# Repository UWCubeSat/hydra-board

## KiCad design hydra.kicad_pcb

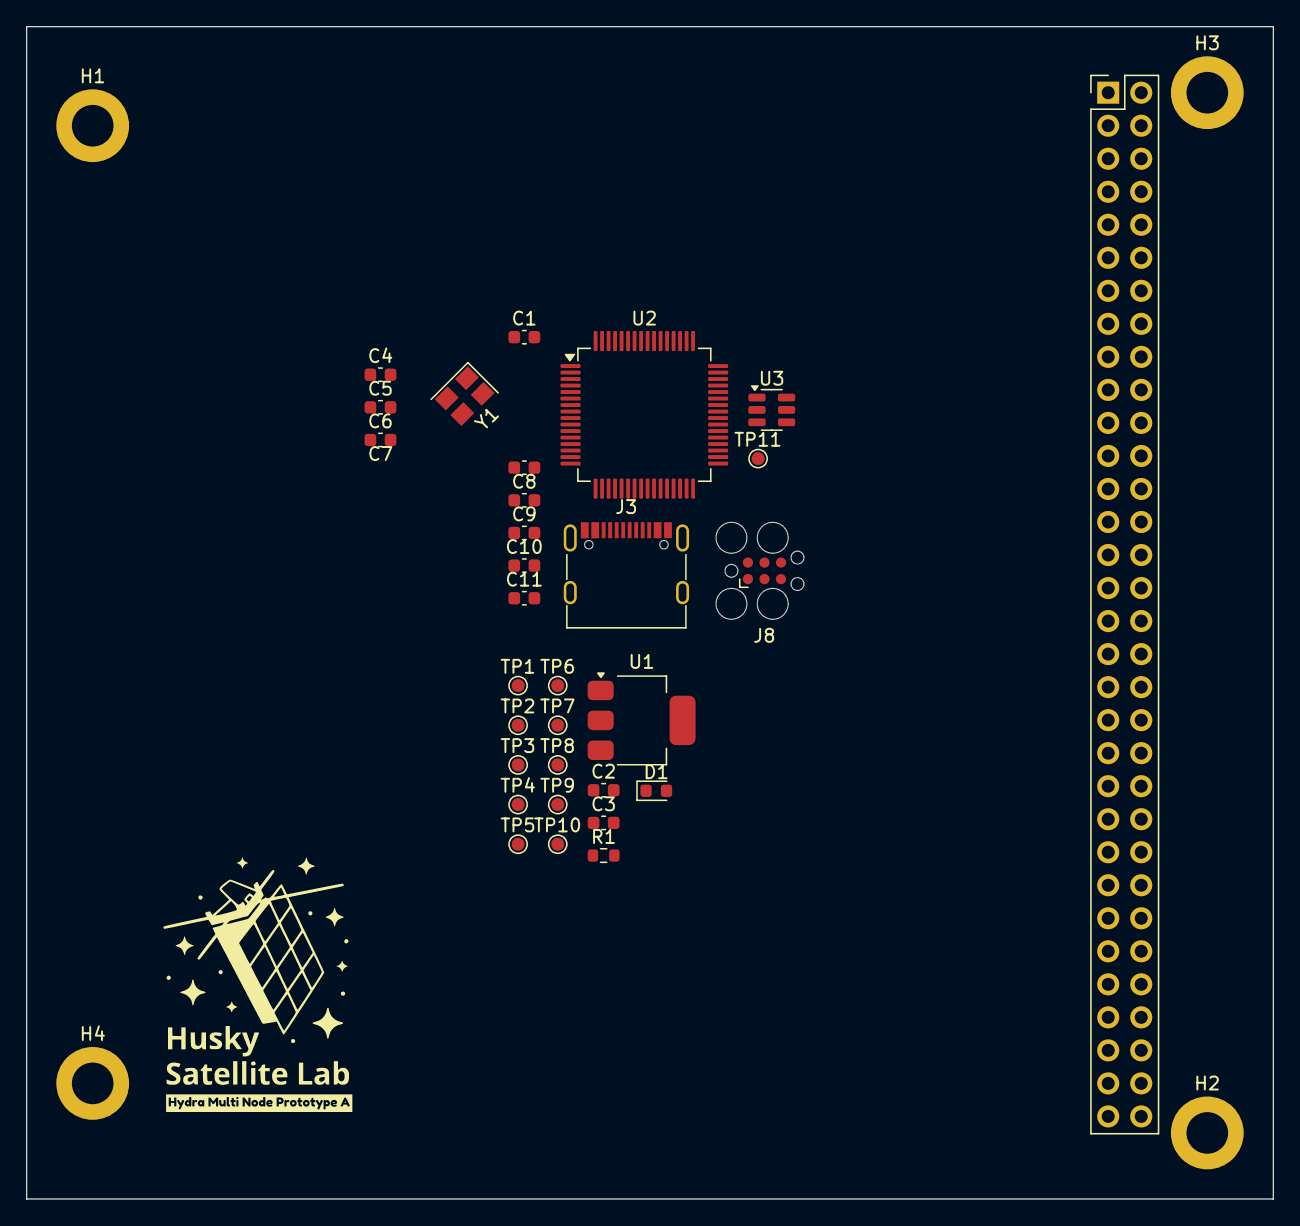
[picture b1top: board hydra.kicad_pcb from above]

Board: 4 copper layers, 95.9 x 90.2 mm, 36 parts (0 on the bottom side), 38 nets, no tracks yet.

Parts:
C1, C11: 3pF; C_0603_1608Metric
C2: 10uF; C_0603_1608Metric
C3: 22uF; C_0603_1608Metric
C4: 4.7uF; C_0603_1608Metric
C5, C6, C7, C8, C9, C10: 0.1uF; C_0603_1608Metric
D1: Power LED; LED_0603_1608Metric
H1, H2, H3, H4: MountingHole; MountingHole_3.2mm_M3_DIN965_Pad
J2: PC104 Interconnect; PinHeader_2x32_P2.54mm_Vertical
J3: USB-C; USB_C_Receptacle_G-Switch_GT-USB-7010ASV
J8: TC2030; Tag-Connect_TC2030-IDC-FP_2x03_P1.27mm_Vertical
R1: 5.1k; R_0603_1608Metric
TP1: 3V3_TP; TestPoint_Pad_D1.0mm
TP2: PSPI_MOSI_TP; TestPoint_Pad_D1.0mm
TP3: PSPI_MISO_TP; TestPoint_Pad_D1.0mm
TP4: PSPI_SCLK_TP; TestPoint_Pad_D1.0mm
TP5: SSPI_MOSI_TP; TestPoint_Pad_D1.0mm
TP6: SSPI_MISO_TP; TestPoint_Pad_D1.0mm
TP7: SSPI_SCLK_TP; TestPoint_Pad_D1.0mm
TP8: RSPI_MOSI_TP; TestPoint_Pad_D1.0mm
TP9: RSPI_MISO_TP; TestPoint_Pad_D1.0mm
TP10: RSPI_SCLK_TP; TestPoint_Pad_D1.0mm
TP11: BOOT1 TP; TestPoint_Pad_D1.0mm
U1: AMS1117-3.3; SOT-223-3_TabPin2
U2: STM32L151RCT6; LQFP-64_10x10mm_P0.5mm
U3: USBLC6-2SC6; SOT-23-6
Y1: 16MHz; Crystal_SMD_3225-4Pin_3.2x2.5mm
kibuzzard-65E19948: G***; kibuzzard-65E19948

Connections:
+3V3: C3.1, C4.1, C5.1, C6.1, C7.1, C8.1, C10.1, D1.2 (A), J8.1 (VCC), TP1.1, U1.2 (VO), U2.1 (VLCD), U2.13 (VDDA), U2.19 (VDD), U2.32 (VDD), U2.48 (VDD), U2.64 (VDD)
/3V3_CONN: C2.1, J2.57, J2.58, U1.3 (VI)
/CS_1: J2.1, J2.2, U2.33 (PB12)
/CS_2: J2.3, J2.4, U2.30 (PB11)
/CS_3: J2.5, J2.6, U2.29 (PB10)
/CS_4: J2.7, J2.8, U2.27 (PB1)
/CS_5: J2.9, J2.10, U2.26 (PB0)
/CS_6: J2.11, J2.12, U2.25 (PC5)
/CS_7: J2.13, J2.14, U2.24 (PC4)
/CS_8: J2.15, J2.16, U2.20 (PA4)
/CS_9: J2.17, J2.18, U2.17 (PA3)
/CS_10: J2.19, J2.20, U2.16 (PA2)
/CS_11: J2.21, J2.22, U2.15 (PA1)
/CS_12: J2.23, J2.24, U2.14 (PA0)
/Node/BOOT1: TP11.1, U2.28 (PB2)
/Node/HSE+: C1.1, U2.5 (PH0), Y1.1
/Node/HSE-: C11.1, U2.6 (PH1), Y1.3
/Node/RESET: C9.1, J8.3 (~RESET), U2.7 (NRST)
/Node/SWD_CLK: J8.4 (SWCLK), U2.49 (PA14)
/Node/SWD_IO: J8.2 (SWDIO), U2.46 (PA13)
/Node/USB_D+: U2.45 (PA12), U3.4 (I/O2)
/Node/USB_D-: U2.44 (PA11), U3.6 (I/O1)
/Node/USB_DT+: J3.A6 (D+), J3.B6 (D+), U3.3 (I/O2)
/Node/USB_DT-: J3.A7 (D-), J3.B7 (D-), U3.1 (I/O1)
/P_MISO: J2.26, TP3.1, U2.35 (PB14)
/P_MOSI: J2.25, TP2.1, U2.36 (PB15)
/P_SCLK: J2.27, TP4.1, U2.34 (PB13)
/R_CS: J2.31, U2.11 (PC3)
/R_MISO: J2.34, TP9.1, U2.52 (PC11)
/R_MOSI: J2.33, TP8.1, U2.53 (PC12)
/R_SCLK: J2.32, TP10.1, U2.51 (PC10)
/S_MISO: J2.30, TP6.1, U2.22 (PA6)
/S_MOSI: J2.29, TP5.1, U2.23 (PA7)
/S_SCLK: J2.28, TP7.1, U2.21 (PA5)
GND: C1.2, C2.2, C3.2, C4.2, C5.2, C6.2, C7.2, C8.2, C9.2, C10.2, C11.2, J3.A1 (GND), J3.A12 (GND), J3.B1 (GND), J3.B12 (GND), J3.S1 (SHIELD), J8.5 (GND), R1.2, U1.1 (GND), U2.12 (VSSA), U2.18 (VSS), U2.31 (VSS), U2.47 (VSS), U2.63 (VSS), U3.2 (GND), Y1.2, Y1.4
unnamed: D1.1 (K), R1.1
unnamed: J2.63, J2.64
unnamed: J3.A4 (VBUS), J3.A9 (VBUS), J3.B4 (VBUS), J3.B9 (VBUS), U3.5 (VBUS)

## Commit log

2024-02-27 feat: initial schematic
    Scaffold of the first board, just the schematic for now. No ERC/DRC
    currently and will need a validation lookover.
2024-02-28 feat: mostly done pcb
2024-02-29 feat: trying multinodal
2024-03-01 feat: more routing
2024-03-01 feat: mostly put together multinode
2024-03-03 feat: in progress rework
2024-03-03 chore: remove hydra symn lib
2024-03-04 feat: trying out a diff mcu
2024-04-05 Rearrange certain components
2024-04-06 switch to STM32L431
